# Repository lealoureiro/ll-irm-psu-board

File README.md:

### Schematic and PCB Design for a breakout board for Mean Well PSU IRM-03 Series.

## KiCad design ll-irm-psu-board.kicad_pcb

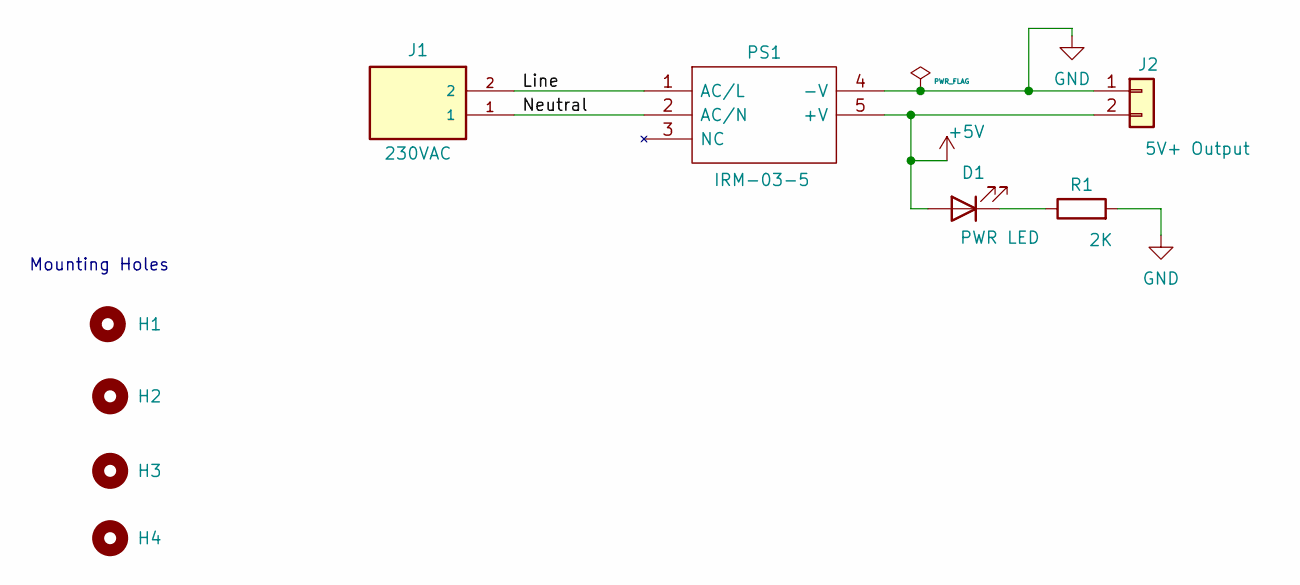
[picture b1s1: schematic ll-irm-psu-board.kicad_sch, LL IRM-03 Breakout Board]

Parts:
D1: PWR LED; LED_D5.0mm
H1, H2, H3, H4: MountingHole; MountingHole_3.2mm_M3_ISO7380
J1: 230VAC; SHDR2W110P0X500_1X2_1000X1120X; MANUFACTURER_PART_NUMBER 1711026; MOUSER_PART_NUMBER 651-1711026
J2: 5V+ Output; JST_XH_B2B-XH-A_1x02_P2.50mm_Vertical
PS1: IRM-03-5; IRM0312; Manufacturer_Part_Number IRM-03-5; Mouser Part Number 709-IRM03-5
R1: 2K; R_Axial_DIN0207_L6.3mm_D2.5mm_P7.62mm_Horizontal

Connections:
+5V: D1.2 (A), J2.2, PS1.5 (+V)
/Line: J1.2, PS1.1 (AC/L)
/Neutral: J1.1, PS1.2 (AC/N)
GND: J2.1, PS1.4 (-V), R1.2
unnamed: D1.1 (K), R1.1

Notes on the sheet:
Mounting Holes

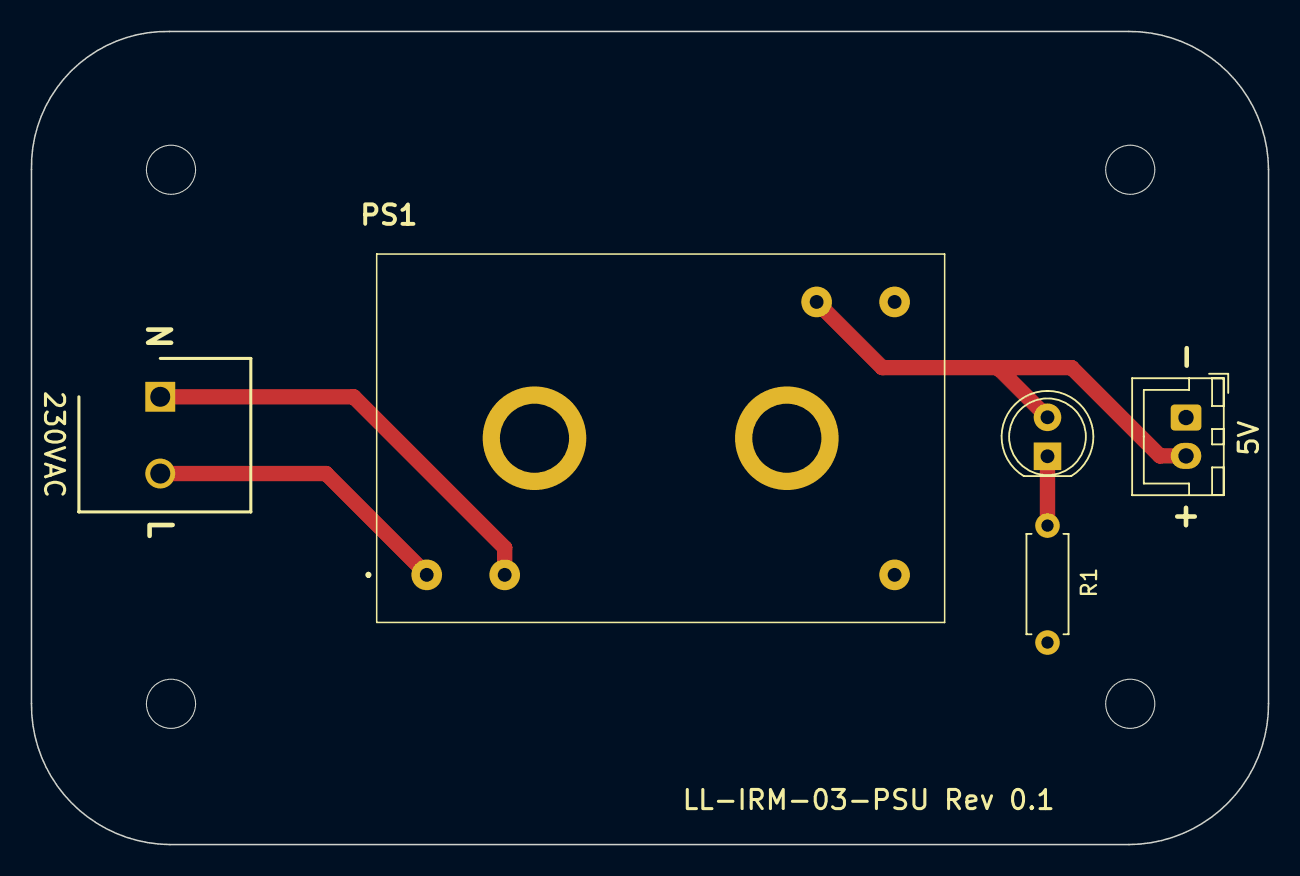
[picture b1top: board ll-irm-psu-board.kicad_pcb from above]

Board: 2 copper layers, 80.6 x 53.0 mm, 9 parts (0 on the bottom side), 5 nets.

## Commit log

2022-11-25 adding initial project structure
2022-11-25 adding gitignore setting page configuration
2022-11-25 adding readme
2022-11-25 adding schematic
2022-11-27 adding footprint details
2022-11-27 adding IRM-03-5 models
2022-11-27 adding phoenix connector models
2022-11-27 adding gerber files
2022-11-27 adding component placing adding routing adding final touches
